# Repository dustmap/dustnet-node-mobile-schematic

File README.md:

# dustnet-node-mobile-schematic
Hardware schematics for Mobile Dustmap Air Quality Sensor Node (SPS30)

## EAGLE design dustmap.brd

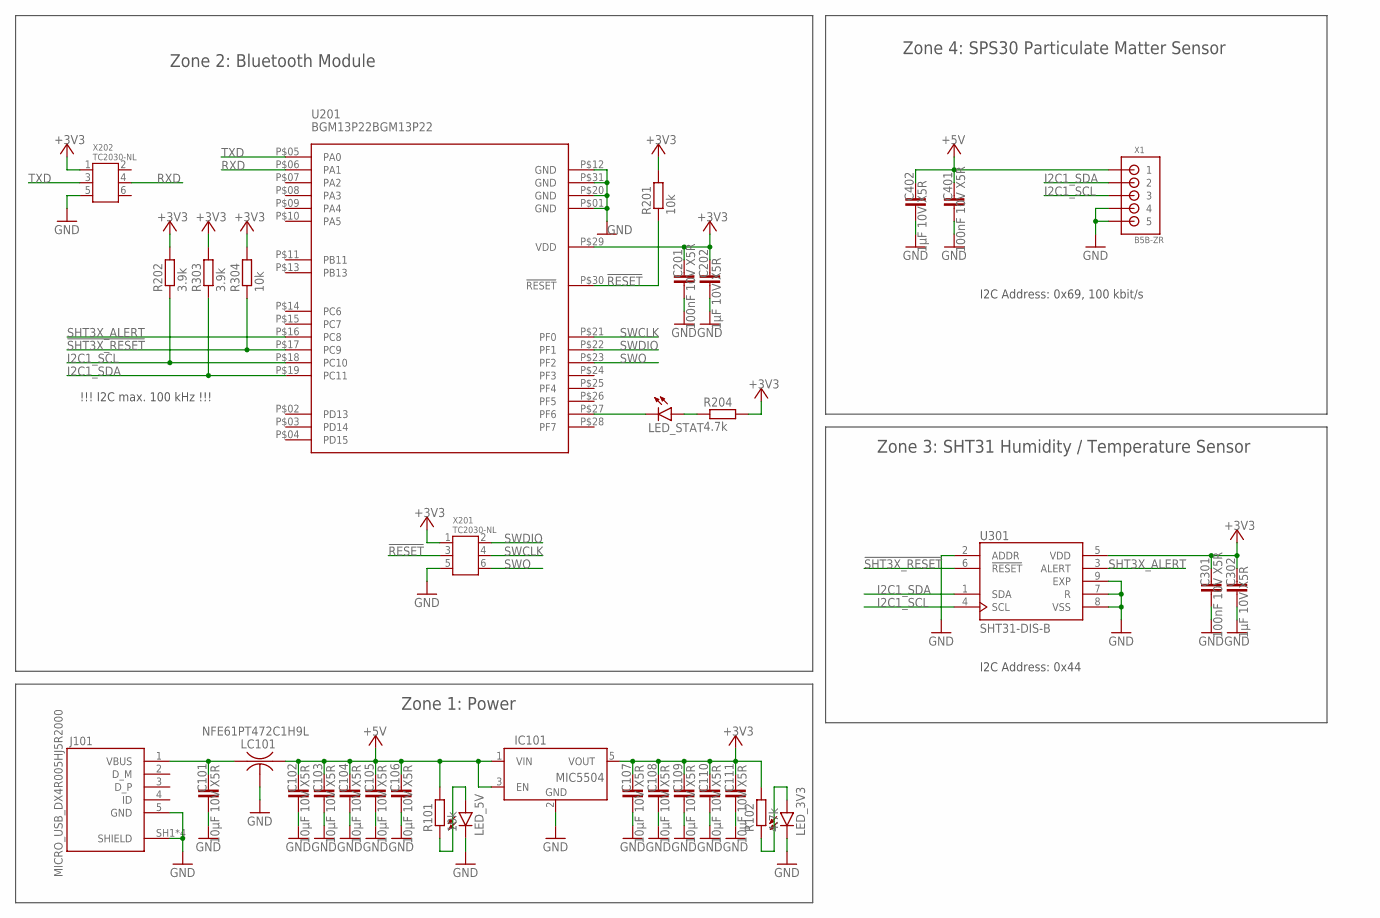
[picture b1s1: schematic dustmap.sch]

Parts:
C101, C102, C103, C104, C105, C106, C107, C108, C109, C110, C111: 10µF 10V X5R; C0603
C201, C301, C401: 100nF 10V X5R; C0603
C202, C302, C402: 1µF 10V X5R; C0603
IC101: MIC5504; SOT23-5
J101: MICRO_USB_DX4R005HJ5R2000; JAE_DX4R005HJ5R2000
LC101: NFE61PT472C1H9L; CAP_NFE61P_6P8X1P6
LED_3V3, LED_5V: LEDCHIP-LED0603; CHIP-LED0603
LED_STAT: LEDCHIP-LED0603; CHIP-LED0603
R101, R201, R304: 10k; R0603
R102, R204: 4.7k; R0603
R202, R303: 3.9k; R0603
U201: BGM13P22BGM13P22; BGM13P22
U301: SHT31-DIS-B; SON50P250X250X100-9N
X1: B5B-ZR
X201, X202: TC2030-NL

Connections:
!RESET: R201.1, U201.P$30 (!RESET), X201.3
!SHT3X_RESET: R304.1, U201.P$17 (PC9), U301.6 (!RESET)
+3V3: C107.1, C108.1, C109.1, C110.1, C111.1, C201.1, C202.1, C301.1, C302.1, IC101.5 (VOUT), R102.2, R201.2, R202.2, R204.2, R303.2, R304.2, U201.P$29 (VDD), U301.5 (VDD), X201.1, X202.1
+5V: C102.1, C103.1, C104.1, C105.1, C106.1, C401.1, C402.1, IC101.1 (VIN), IC101.3 (EN), LC101.3, R101.2, X1.1
GND: C101.2, C102.2, C103.2, C104.2, C105.2, C106.2, C107.2, C108.2, C109.2, C110.2, C111.2, C201.2, C202.2, C301.2, C302.2, C401.2, C402.2, IC101.2 (GND), J101.5 (GND), J101.SH1 (SHIELD), J101.SH2 (SHIELD), J101.SH3 (SHIELD), J101.SH4 (SHIELD), LC101.2, LED_3V3.C, LED_5V.C, U201.P$01 (GND), U201.P$12 (GND), U201.P$20 (GND), U201.P$31 (GND), U301.2 (ADDR), U301.7 (R), U301.8 (VSS), U301.9 (EXP), X1.4, X1.5, X201.5, X202.5
I2C1_SCL: R202.1, U201.P$18 (PC10), U301.4 (SCL), X1.3
I2C1_SDA: R303.1, U201.P$19 (PC11), U301.1 (SDA), X1.2
unnamed: LED_5V.A, R101.1
unnamed: C101.1, J101.1 (VBUS), LC101.1
unnamed: LED_STAT.C, U201.P$27 (PF6)
unnamed: LED_STAT.A, R204.1
unnamed: LED_3V3.A, R102.1
RXD: U201.P$06 (PA1), X202.4
SHT3X_ALERT: U201.P$16 (PC8), U301.3 (ALERT)
SWCLK: U201.P$21 (PF0), X201.4
SWDIO: U201.P$22 (PF1), X201.2
SWO: U201.P$23 (PF2), X201.6
TXD: U201.P$05 (PA0), X202.3

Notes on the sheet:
Zone 1: Power
Zone 3: SHT31 Humidity / Temperature Sensor
Zone 2: Bluetooth Module
Zone 4: SPS30 Particulate Matter Sensor
I2C Address: 0x44
I2C Address: 0x69, 100 kbit/s
!!! I2C max. 100 kHz !!!

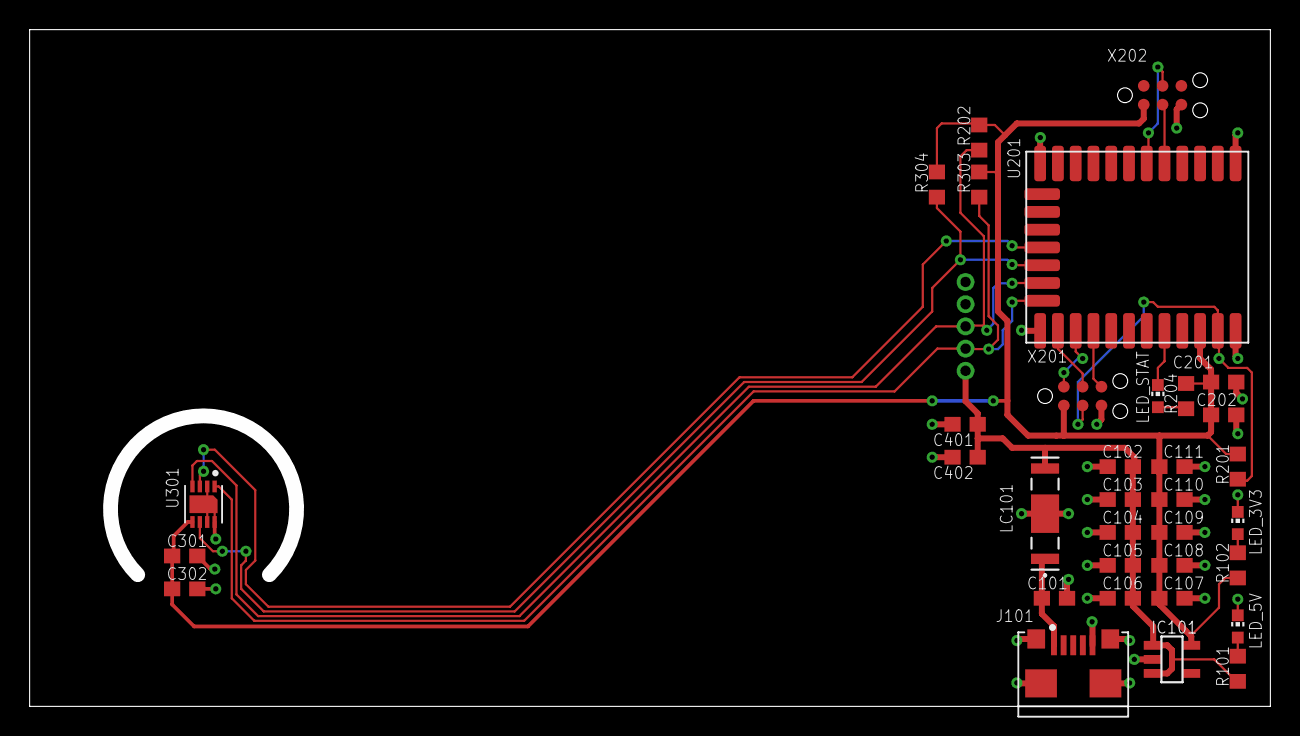
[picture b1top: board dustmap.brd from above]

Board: 2 copper layers, 82.8 x 44.7 mm, 35 parts (1 on the bottom side), 18 nets.

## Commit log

2019-09-02 Added Schematics and Board
2019-09-02 Added Licence
